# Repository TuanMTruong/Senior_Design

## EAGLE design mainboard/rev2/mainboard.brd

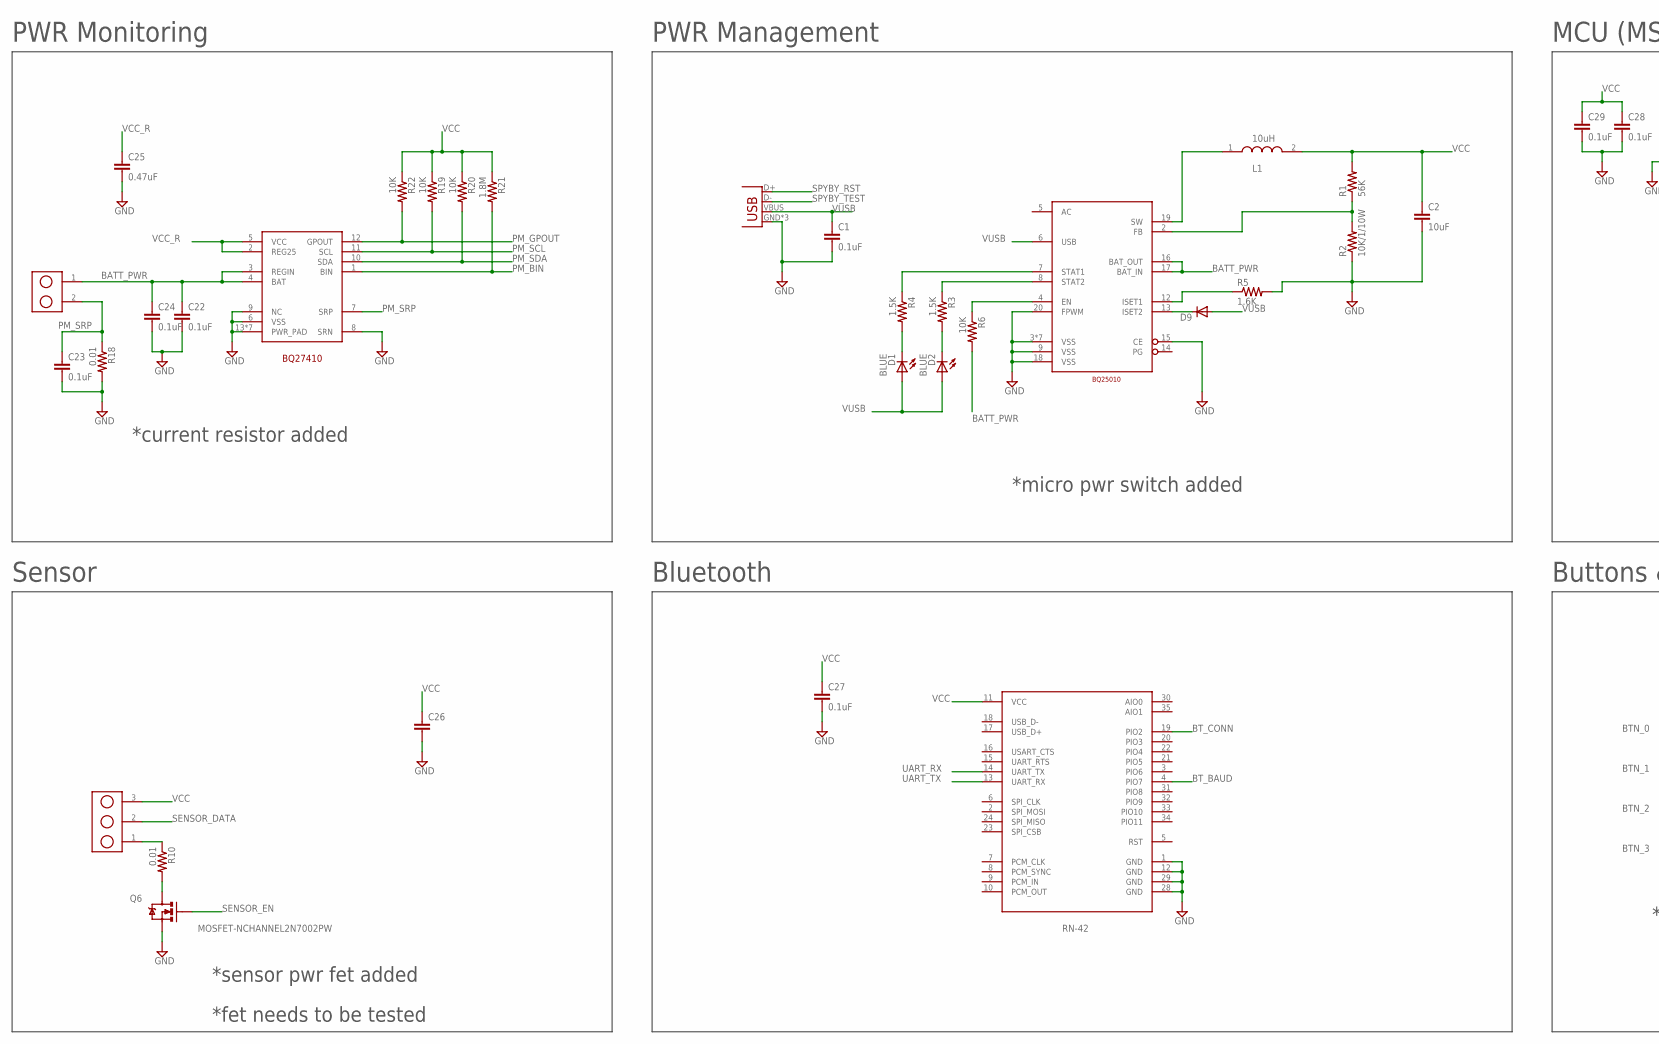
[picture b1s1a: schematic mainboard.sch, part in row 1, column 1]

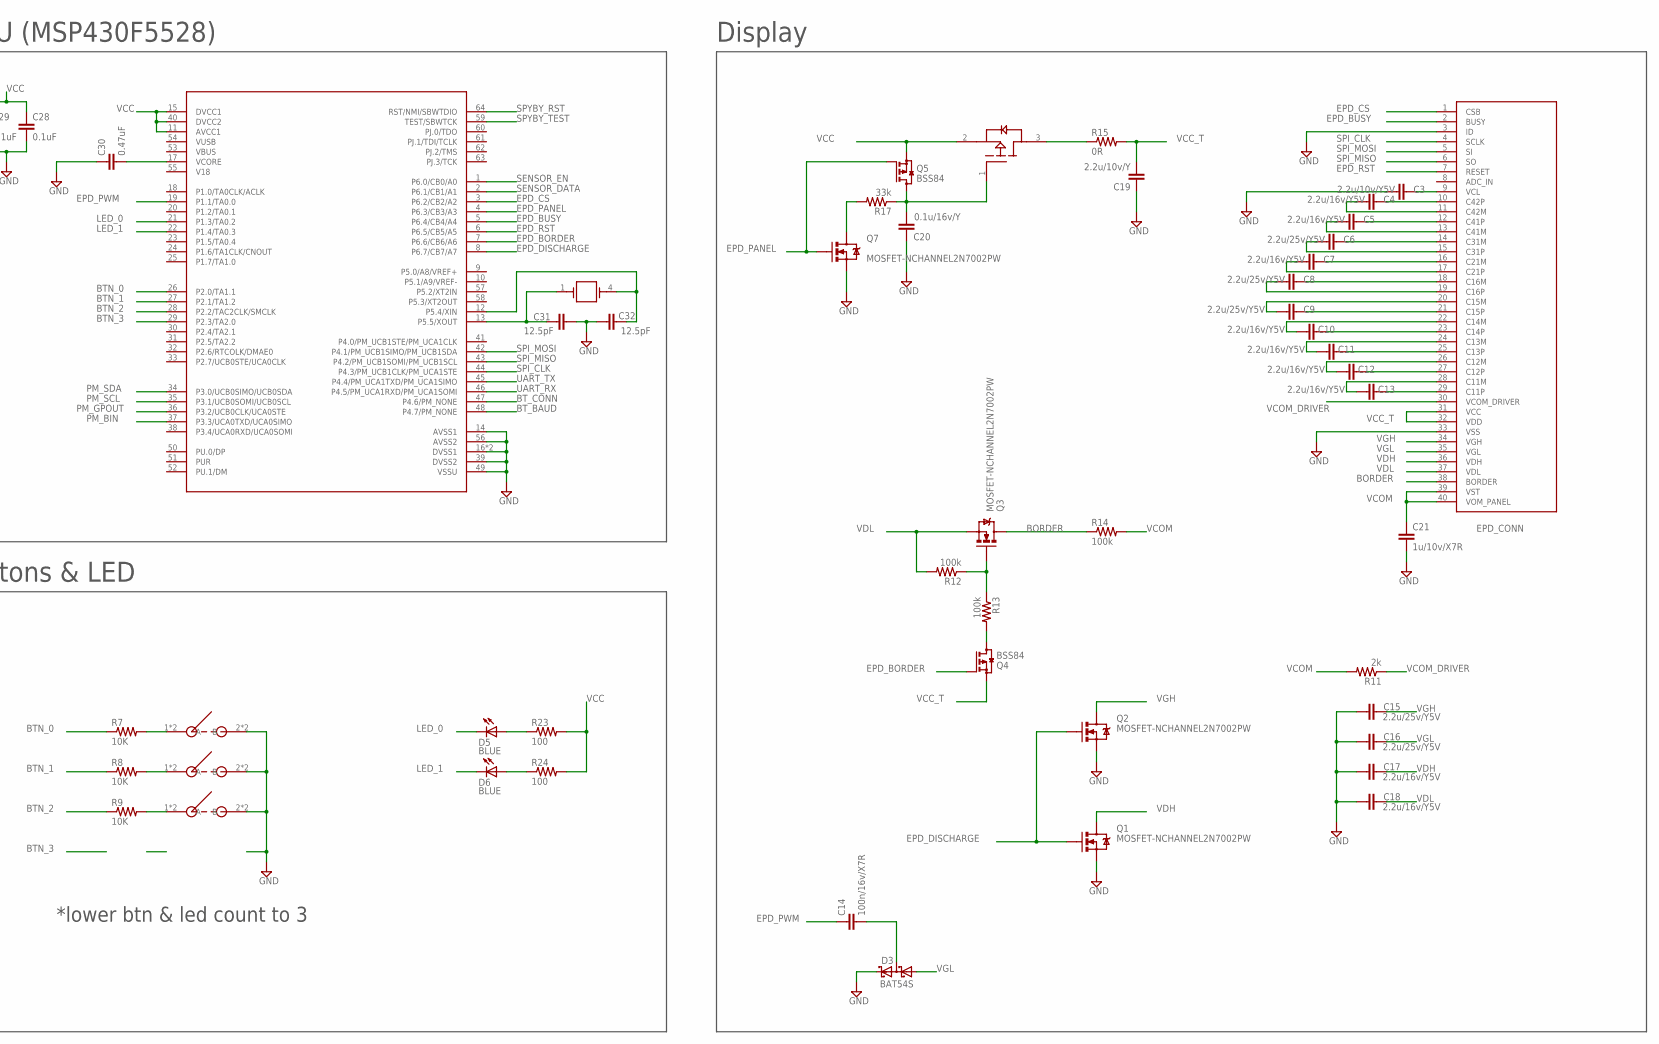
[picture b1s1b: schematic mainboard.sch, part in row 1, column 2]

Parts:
AP2305: DMG2305UX; SOT23
C1, C22, C23, C24, C27, C28, C29: 0.1uF; 0402-CAP
C2: 10uF; 0402-CAP
C3: 2.2u/10v/Y5V; 0402-CAP
C4, C5, C7, C10, C11, C12, C13, C17, C18: 2.2u/16v/Y5V; 0402-CAP
C6, C8, C9, C15, C16: 2.2u/25v/Y5V; 0402-CAP
C14: 100n/16v/X7R; 0402-CAP
C19: 2.2u/10v/Y; 0402-CAP
C20: 0.1u/16v/Y; 0402-CAP
C21: 1u/10v/X7R; 0402-CAP
C25, C30: 0.47uF; 0402-CAP
C26: CAP0402-CAP; 0402-CAP
C31, C32: 12.5pF; 0402-CAP
D1, D2, D5, D6: BLUE; LED-0603
D3: BAT54S; SOT23
D9: DIODESOD523; SOD523
JP1: USB-MICROB
L1: 10uH; ASPI_0428S-100M-T
Q1, Q2, Q3, Q6, Q7: MOSFET-NCHANNEL2N7002PW; SOT323
Q4, Q5: BSS84; SOT23
R1: 56K; 0402-RES
R2: 10K/1/10W; 0402-RES
R3, R4: 1.5K; 0402-RES
R5: 1.6K; 0402-RES
R6, R7, R8, R9, R19, R20, R22: 10K; 0402-RES
R10, R18: 0.01; 0402-RES
R11: 2k; 0402-RES
R12, R13, R14: 100k; 0402-RES
R15: 0R; 0402-RES
R17: 33k; 0402-RES
R21: 1.8M; 0402-RES
R23, R24: 100; 0402-RES
U$1: MSP430F5528; VQFN_RGC_64PIN
U$2: RN-42
U$3: BQ25010; VQFN_RHL_20PIN
U$4, U$5, U$6: RA_TAC_BUTTON"EVQPUK"; EVQ-PUK02K; PART# EVQ-PUK02K
U$8: FH12-40S-0.5SH
U$9: BQ27410; SON_DRZ_12PIN
U$11: HEADER_2PIN_50MIL
U$12: HEADER_3PIN_50MIL
X1: CRYSTAL"32.768"; ECS-327-12.5-17X-C-TR

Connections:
BATT_PWR: C22.1, C24.1, R6.2, U$3.16 (BAT_OUT), U$3.17 (BAT_IN), U$9.3 (REGIN), U$9.4 (BAT), U$11.1
BORDER: Q3.3 (D), R14.1, U$8.38 (BORDER)
BTN_0: R7.1, U$1.26 (P2.0/TA1.1)
BTN_1: R8.1, U$1.27 (P2.1/TA1.2)
BTN_2: R9.1, U$1.28 (P2.2/TAC2CLK/SMCLK)
BTN_3: U$1.29 (P2.3/TA2.0)
BT_BAUD: U$1.48 (P4.7/PM_NONE), U$2.4 (PIO7)
BT_CONN: U$1.47 (P4.6/PM_NONE), U$2.19 (PIO2)
EPD_BORDER: Q4.1 (G), U$1.7 (P6.6/CB6/A6)
EPD_BUSY: U$1.5 (P6.4/CB4/A4), U$8.2 (BUSY)
EPD_CS: U$1.3 (P6.2/CB2/A2), U$8.1 (CSB)
EPD_DISCHARGE: Q1.1 (G), Q2.1 (G), U$1.8 (P6.7/CB7/A7)
EPD_PANEL: Q5.1 (G), Q7.1 (G), U$1.4 (P6.3/CB3/A3)
EPD_PWM: C14.1, U$1.19 (P1.1/TA0.0)
EPD_RST: U$1.6 (P6.5/CB5/A5), U$8.7 (RESET)
GND: C1.2, C2.2, C3.1, C15.1, C16.1, C17.1, C18.1, C19.1, C20.1, C21.2, C22.2, C23.2, C24.2, C25.2, C26.2, C27.2, C28.2, C29.2, C30.1, C31.2, C32.1, D3.2 (C2), JP1.GND, JP1.MT1 (GND), JP1.MT2 (GND), Q1.2 (S), Q2.2 (S), Q6.2 (S), Q7.2 (S), R2.1, R5.2, R18.2, U$1.14 (AVSS1), U$1.16 (DVSS1), U$1.39 (DVSS2), U$1.49 (VSSU), U$1.56 (AVSS2), U$1.P$1 (DVSS1), U$2.1 (GND), U$2.12 (GND), U$2.28 (GND), U$2.29 (GND), U$3.3 (VSS), U$3.9 (VSS), U$3.15 (CE), U$3.18 (VSS), U$3.20 (FPWM), U$3.P$21 (VSS), U$3.P$22 (VSS), U$3.P$23 (VSS), U$3.P$24 (VSS), U$3.P$25 (VSS), U$3.P$26 (VSS), U$4.2 (B), U$4.4 (B), U$5.2 (B), U$5.4 (B), U$6.2 (B), U$6.4 (B), U$8.3 (ID), U$8.33 (VSS), U$9.6 (VSS), U$9.8 (SRN), U$9.9 (NC), U$9.13 (PWR_PAD), U$9.P$15 (PWR_PAD), U$9.P$16 (PWR_PAD), U$9.P$17 (PWR_PAD), U$9.P$18 (PWR_PAD), U$9.P$19 (PWR_PAD), U$9.P$20 (PWR_PAD)
LED_0: D5.C, U$1.21 (P1.3/TA0.2)
LED_1: D6.C, U$1.22 (P1.4/TA0.3)
unnamed: R5.1, U$3.12 (ISET1)
unnamed: D1.C, R4.2
unnamed: D9.C, U$3.13 (ISET2)
unnamed: D2.C, R3.2
unnamed: R1.1, R2.2, U$3.2 (FB)
unnamed: L1.1, U$3.19 (SW)
unnamed: C30.2, U$1.17 (VCORE)
unnamed: Q4.3 (D), R13.2
unnamed: C14.2, D3.3 (C1A2)
unnamed: R4.1, U$3.7 (STAT1)
unnamed: R3.1, U$3.8 (STAT2)
unnamed: R6.1, U$3.4 (EN)
unnamed: R7.2, U$4.1 (A), U$4.3 (A)
unnamed: R8.2, U$5.1 (A), U$5.3 (A)
unnamed: R9.2, U$6.1 (A), U$6.3 (A)
unnamed: Q6.3 (D), R10.2
unnamed: R10.1, U$12.1
unnamed: C4.2, U$8.10 (C42P)
unnamed: C4.1, U$8.11 (C42M)
unnamed: C5.2, U$8.12 (C41P)
unnamed: C5.1, U$8.13 (C41M)
unnamed: C6.2, U$8.14 (C31M)
unnamed: C6.1, U$8.15 (C31P)
unnamed: C7.2, U$8.16 (C21M)
unnamed: C7.1, U$8.17 (C21P)
unnamed: C8.2, U$8.18 (C16M)
unnamed: C8.1, U$8.19 (C16P)
unnamed: C9.1, U$8.20 (C15M)
unnamed: C9.2, U$8.21 (C15P)
unnamed: C10.1, U$8.22 (C14M)
unnamed: C10.2, U$8.23 (C14P)
unnamed: C11.1, U$8.24 (C13M)
unnamed: C11.2, U$8.25 (C13P)
unnamed: C12.1, U$8.26 (C12M)
unnamed: C12.2, U$8.27 (C12P)
unnamed: C13.1, U$8.28 (C11M)
unnamed: C13.2, U$8.29 (C11P)
unnamed: C3.2, U$8.9 (VCL)
unnamed: AP2305.3 (DRAIN), R15.1
unnamed: D5.A, R23.1
unnamed: Q3.1 (G), R12.1, R13.1
unnamed: AP2305.1 (GATE), C20.2, Q5.3 (D), R17.1
unnamed: D6.A, R24.1
unnamed: Q7.3 (D), R17.2
PM_BIN: R21.2, U$1.37 (P3.3/UCA0TXD/UCA0SIMO), U$9.1 (BIN)
PM_GPOUT: R22.2, U$1.36 (P3.2/UCB0CLK/UCA0STE), U$9.12 (GPOUT)
PM_SCL: R19.2, U$1.35 (P3.1/UCB0SOMI/UCB0SCL), U$9.11 (SCL)
PM_SDA: R20.2, U$1.34 (P3.0/UCB0SIMO/UCB0SDA), U$9.10 (SDA)
PM_SRP: C23.1, R18.1, U$9.7 (SRP), U$11.2
SENSOR_DATA: U$1.2 (P6.1/CB1/A1), U$12.2
SENSOR_EN: Q6.1 (G), U$1.1 (P6.0/CB0/A0)
SPI_CLK: U$1.44 (P4.3/PM_UCB1CLK/PM_UCA1STE), U$8.4 (SCLK)
SPI_MISO: U$1.43 (P4.2/PM_UCB1SOMI/PM_UCB1SCL), U$8.6 (SO)
SPI_MOSI: U$1.42 (P4.1/PM_UCB1SIMO/PM_UCB1SDA), U$8.5 (SI)
SPYBY_RST: JP1.D+, U$1.64 (RST/NMI/SBWTDIO)
SPYBY_TEST: JP1.D-, U$1.59 (TEST/SBWTCK)
UART_RX: U$1.46 (P4.5/PM_UCA1RXD/PM_UCA1SOMI), U$2.14 (UART_TX)
UART_TX: U$1.45 (P4.4/PM_UCA1TXD/PM_UCA1SIMO), U$2.13 (UART_RX)
VCC: AP2305.2 (SOURCE), C2.1, C26.1, C27.1, C28.1, C29.1, L1.2, Q5.2 (S), R1.2, R19.1, R20.1, R21.1, R22.1, R23.2, R24.2, U$1.11 (AVCC1), U$1.15 (DVCC1), U$1.40 (DVCC2), U$2.11 (VCC), U$12.3
VCC_R: C25.1, U$9.2 (REG25), U$9.5 (VCC)
VCC_T: C19.2, Q4.2 (S), R15.2, U$8.31 (VCC), U$8.32 (VDD)
VCOM: C21.1, R11.2, R14.2, U$8.39 (VST), U$8.40 (VOM_PANEL)
VCOM_DRIVER: R11.1, U$8.30 (VCOM_DRIVER)
VDH: C17.2, Q1.3 (D), U$8.36 (VDH)
VDL: C18.2, Q3.2 (S), R12.2, U$8.37 (VDL)
VGH: C15.2, Q2.3 (D), U$8.34 (VGH)
VGL: C16.2, D3.1 (A1), U$8.35 (VGL)
VUSB: C1.1, D1.A, D2.A, D9.A, JP1.VBUS, U$3.6 (USB)
XIN: C32.2, U$1.12 (P5.4/XIN), X1.4
XOUT: C31.1, U$1.13 (P5.5/XOUT), X1.1

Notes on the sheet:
MCU (MSP430F5528)
PWR Management
Bluetooth
Buttons & LED
Sensor
Display
PWR Monitoring
10uH
*micro pwr switch added
*sensor pwr fet added
*fet needs to be tested
*current resistor added
*lower btn & led count to 3

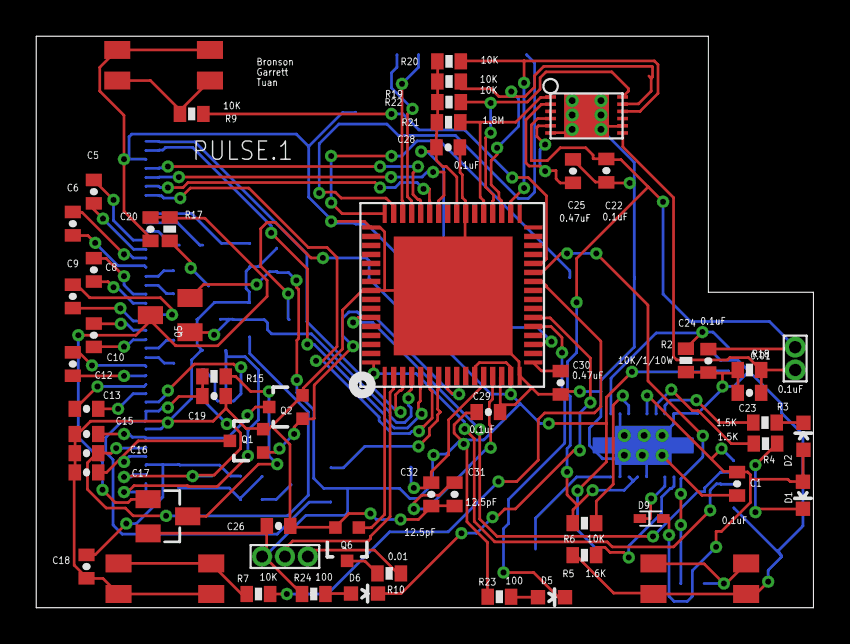
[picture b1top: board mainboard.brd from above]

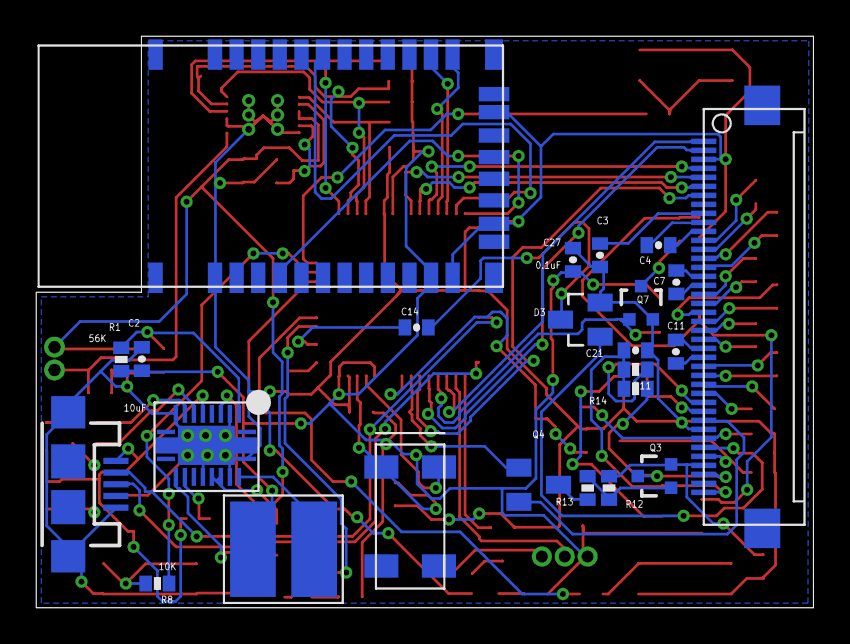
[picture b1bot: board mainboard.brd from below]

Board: 2 copper layers, 43.2 x 31.8 mm, 82 parts (24 on the bottom side), 87 nets.

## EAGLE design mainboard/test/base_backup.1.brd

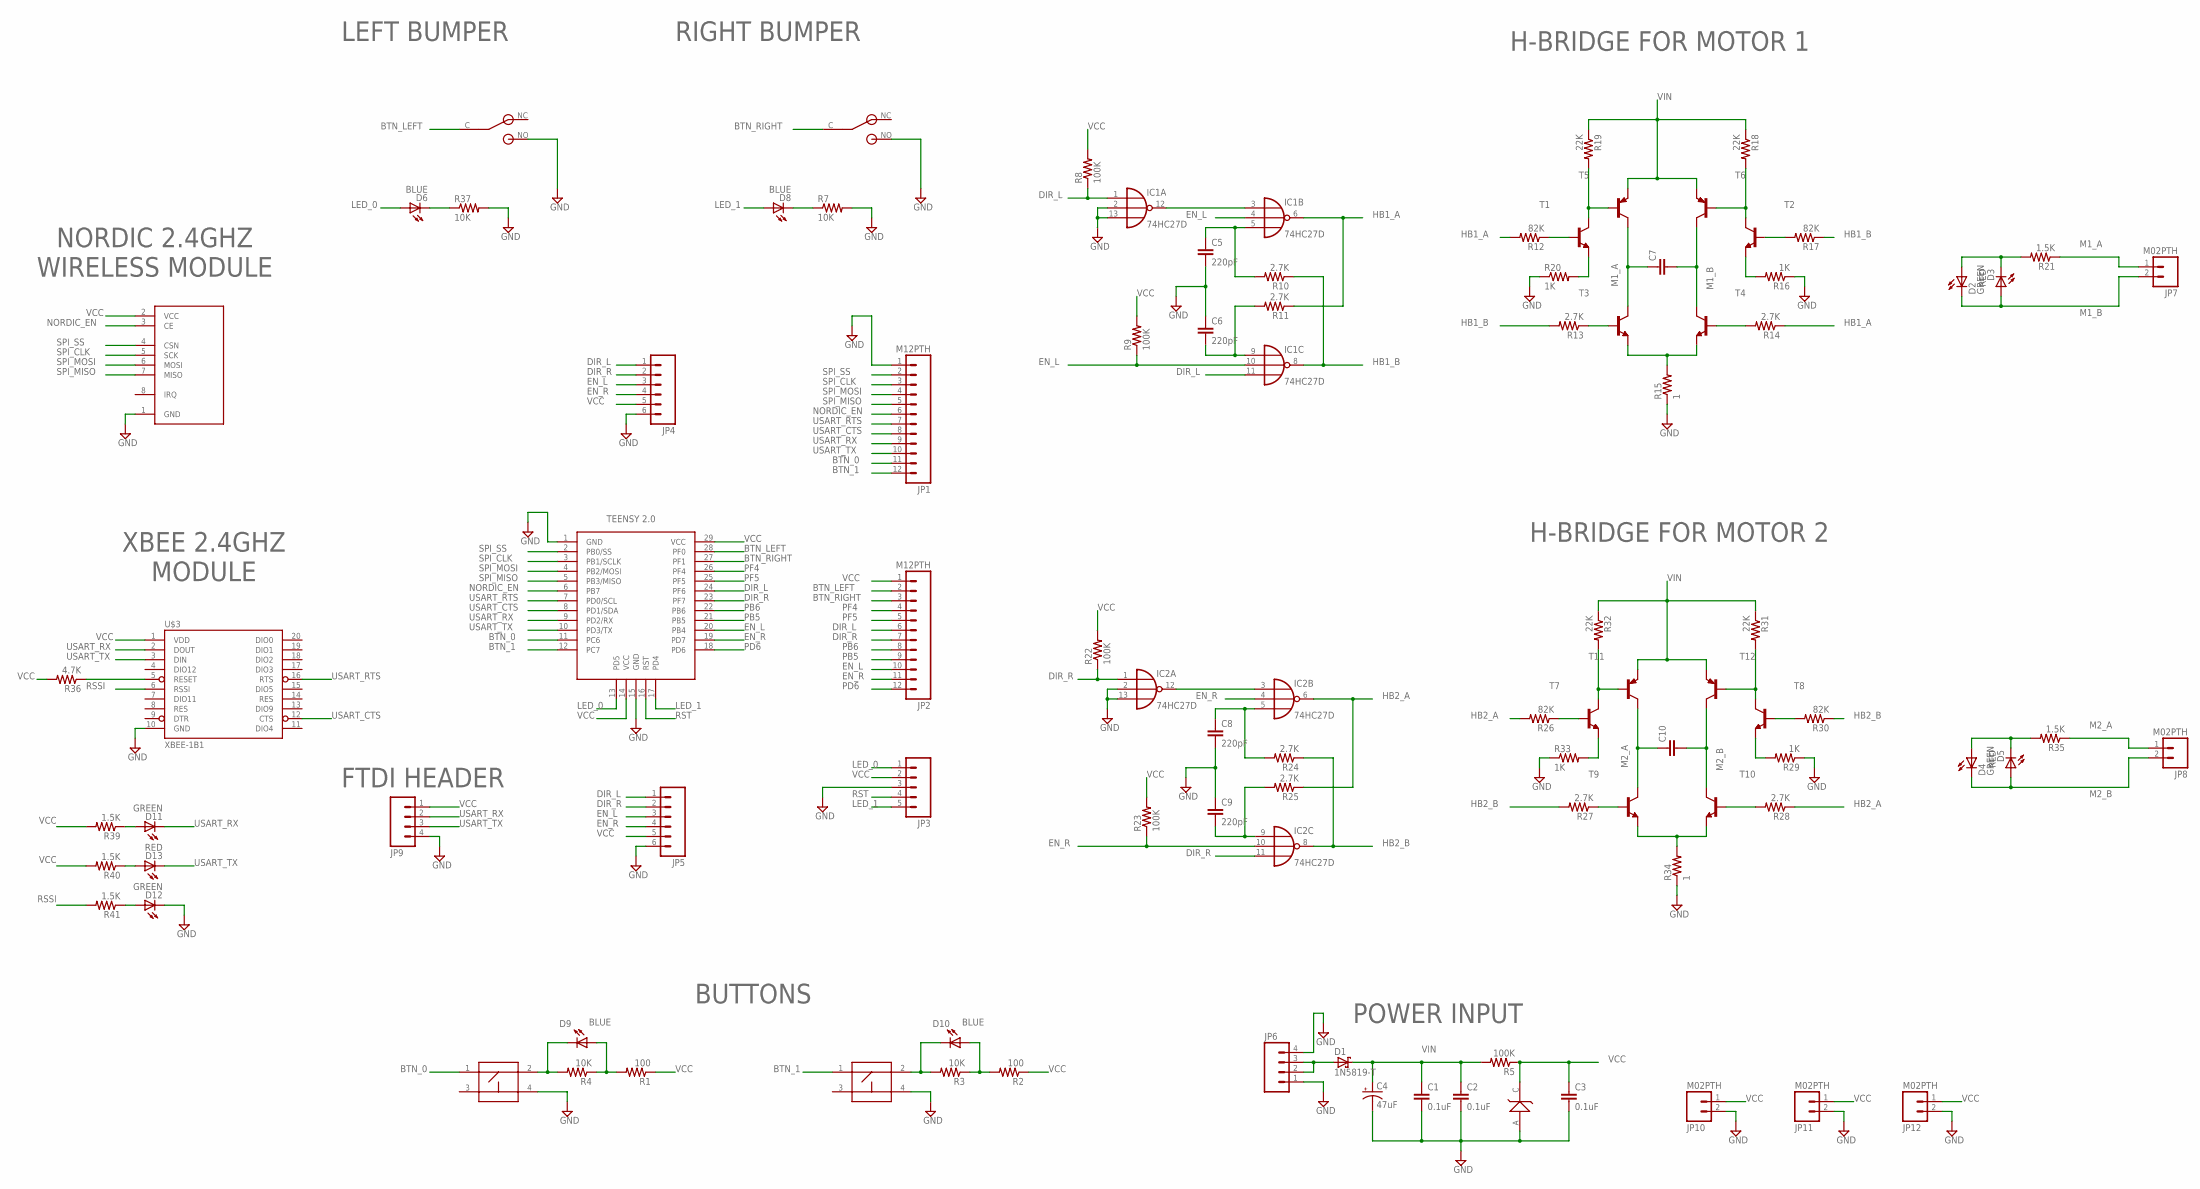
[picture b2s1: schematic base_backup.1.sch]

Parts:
C1, C2, C3: 0.1uF; 0603-CAP
C4: 47uF; PANASONIC_C
C5, C6, C8, C9: 220pF; 0603-CAP
C7, C10: CAP0603-CAP; 0603-CAP
D1: 1N5819-T; DO41-7.6
D2, D4, D11, D12: GREEN; LED-0603
D3, D5, D13: RED; LED-0603
D6, D8, D9, D10: BLUE; LED-0603
D7: 1N5819; DO41-7.6
IC1, IC2: 74HC27D; SO14
JP1, JP2: M12PTH; 1X12
JP3: M05PTH; 1X05
JP4, JP5: M06SIP; 1X06
JP6, JP9: M04PTH; 1X04
JP7, JP8, JP10, JP11, JP12: M02PTH; 1X02
R1, R2: 100; 0603-RES
R3, R4, R7, R37: 10K; 0603-RES
R5, R8, R9, R22, R23: 100K; 0603-RES
R10, R11, R13, R14, R24, R25, R27, R28: 2.7K; 0603-RES
R12, R17, R26, R30: 82K; 0603-RES
R15, R34: 1; 0603-RES
R16, R20, R29, R33: 1K; 0603-RES
R18, R19, R31, R32: 22K; 0603-RES
R21, R35, R39, R40, R41: 1.5K; 0603-RES
R36: 4.7K; 0603-RES
T1, T2, T3, T4, T7, T8, T9, T10: MMBT4401LT1-NPN-SOT23-BEC; SOT23-BEC
T5, T6, T11, T12: MMBT4403LT1-PNP-SOT23-BEC; SOT23-BEC
U$1: TEENSY2.0
U$2: NRF24L01
U$3: XBEE-1B1; XBEE-1
U$4, U$5: SPARKFUN_TAC_BUTTONS
U$6, U$7: SS075Q103F_BTN_RA; SS075Q103F020V1A

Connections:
BTN_0: JP1.11, U$1.11 (PC6), U$4.1
BTN_1: JP1.12, U$1.12 (PC7), U$5.1
BTN_LEFT: JP2.2, U$1.28 (PF0), U$6.C (COM)
BTN_RIGHT: JP2.3, U$1.27 (PF1), U$7.C (COM)
DIR_L: IC1.1 (I0), IC1.11 (I2), JP2.6, JP4.1, JP5.1, R8.1, U$1.24 (PF6)
DIR_R: IC2.1 (I0), IC2.11 (I2), JP2.7, JP4.2, JP5.2, R22.1, U$1.23 (PF7)
EN_L: IC1.4 (I1), IC1.10 (I1), JP2.10, JP4.3, JP5.3, R9.1, U$1.20 (PB4)
EN_R: IC2.4 (I1), IC2.10 (I1), JP2.11, JP4.4, JP5.4, R23.1, U$1.19 (PD7)
GND: C1.2, C2.2, C3.2, C4.-, C5.2, C6.1, C8.2, C9.1, D7.A, D12.C, IC1.2 (I1), IC1.7 (GND), IC1.13 (I2), IC2.2 (I1), IC2.7 (GND), IC2.13 (I2), JP1.1, JP3.3, JP4.6, JP5.6, JP6.1, JP6.4, JP9.4, JP10.2, JP11.2, JP12.2, R7.2, R15.1, R16.1, R20.1, R29.1, R33.1, R34.1, R37.2, U$1.1 (GND), U$1.15 (GND), U$2.1 (GND), U$3.10 (GND), U$4.4, U$5.4, U$6.NO, U$7.NO
HB1_A: IC1.6 (O), R11.1, R12.2, R14.1
HB1_B: IC1.8 (O), R10.1, R13.2, R17.1
HB2_A: IC2.6 (O), R25.1, R26.2, R28.1
HB2_B: IC2.8 (O), R24.1, R27.2, R30.1
LED_0: D6.A, JP3.1, U$1.13 (PD5)
LED_1: D8.A, JP3.5, U$1.17 (PD4)
M1_A: C7.1, JP7.1, R21.1, T3.C, T5.C
M1_B: C7.2, D2.C, D3.A, JP7.2, T4.C, T6.C
M2_A: C10.1, JP8.1, R35.1, T9.C, T11.C
M2_B: C10.2, D4.C, D5.A, JP8.2, T10.C, T12.C
unnamed: IC2.3 (I0), IC2.12 (O)
unnamed: C8.1, IC2.5 (I2), R24.2
unnamed: D9.A, R1.2, R4.1
unnamed: D9.C, R4.2, U$4.2
unnamed: C9.2, IC2.9 (I0), R25.2
unnamed: D10.A, R2.2, R3.1
unnamed: D10.C, R3.2, U$5.2
unnamed: R27.1, T9.B
unnamed: R32.2, T7.C, T11.B
unnamed: R31.2, T8.C, T12.B
unnamed: D1.A, JP6.2, JP6.3
unnamed: D6.C, R37.1
unnamed: D12.A, R41.1
unnamed: D13.A, R40.1
unnamed: D11.A, R39.1
unnamed: R30.2, T8.B
unnamed: C6.2, IC1.9 (I0), R11.2
unnamed: IC1.3 (I0), IC1.12 (O)
unnamed: R26.1, T7.B
unnamed: C5.1, IC1.5 (I2), R10.2
unnamed: R19.2, T1.C, T5.B
unnamed: R28.2, T10.B
unnamed: R20.2, T1.E
unnamed: R34.2, T9.E, T10.E
unnamed: R33.2, T7.E
unnamed: R29.2, T8.E
unnamed: D4.A, D5.C, R35.2
unnamed: R18.2, T2.C, T6.B
unnamed: R17.2, T2.B
unnamed: R13.1, T3.B
unnamed: R12.1, T1.B
unnamed: D8.C, R7.1
unnamed: R14.2, T4.B
unnamed: R15.2, T3.E, T4.E
unnamed: R16.2, T2.E
unnamed: D2.A, D3.C, R21.2
unnamed: R36.1, U$3.5 (RESET)
NORDIC_EN: JP1.6, U$1.6 (PB7), U$2.3 (CE)
PB5: JP2.9, U$1.21 (PB5)
PB6: JP2.8, U$1.22 (PB6)
PD6: JP2.12, U$1.18 (PD6)
PF4: JP2.4, U$1.26 (PF4)
PF5: JP2.5, U$1.25 (PF5)
RSSI: R41.2, U$3.6 (RSSI)
RST: JP3.4, U$1.16 (RST)
SPI_CLK: JP1.3, U$1.3 (PB1/SCLK), U$2.5 (SCK)
SPI_MISO: JP1.5, U$1.5 (PB3/MISO), U$2.7 (MISO)
SPI_MOSI: JP1.4, U$1.4 (PB2/MOSI), U$2.6 (MOSI)
SPI_SS: JP1.2, U$1.2 (PB0/SS), U$2.4 (CSN)
USART_CTS: JP1.8, U$1.8 (PD1/SDA), U$3.12 (CTS)
USART_RTS: JP1.7, U$1.7 (PD0/SCL), U$3.16 (RTS)
USART_RX: D11.C, JP1.9, JP9.2, U$1.9 (PD2/RX), U$3.2 (DOUT)
USART_TX: D13.C, JP1.10, JP9.3, U$1.10 (PD3/TX), U$3.3 (DIN)
VCC: C3.1, D7.C, IC1.14 (VCC), IC2.14 (VCC), JP2.1, JP3.2, JP4.5, JP5.5, JP9.1, JP10.1, JP11.1, JP12.1, R1.1, R2.1, R5.1, R8.2, R9.2, R22.2, R23.2, R36.2, R39.2, R40.2, U$1.14 (VCC), U$1.29 (VCC), U$2.2 (VCC), U$3.1 (VDD)
VIN: C1.1, C2.1, C4.+, D1.C, R5.2, R18.1, R19.1, R31.1, R32.1, T5.E, T6.E, T11.E, T12.E

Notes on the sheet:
LEFT BUMPER
RIGHT BUMPER
NORDIC 2.4GHZ WIRELESS MODULE
XBEE 2.4GHZ MODULE
FTDI HEADER
BUTTONS
POWER INPUT
H-BRIDGE FOR MOTOR 1
H-BRIDGE FOR MOTOR 2

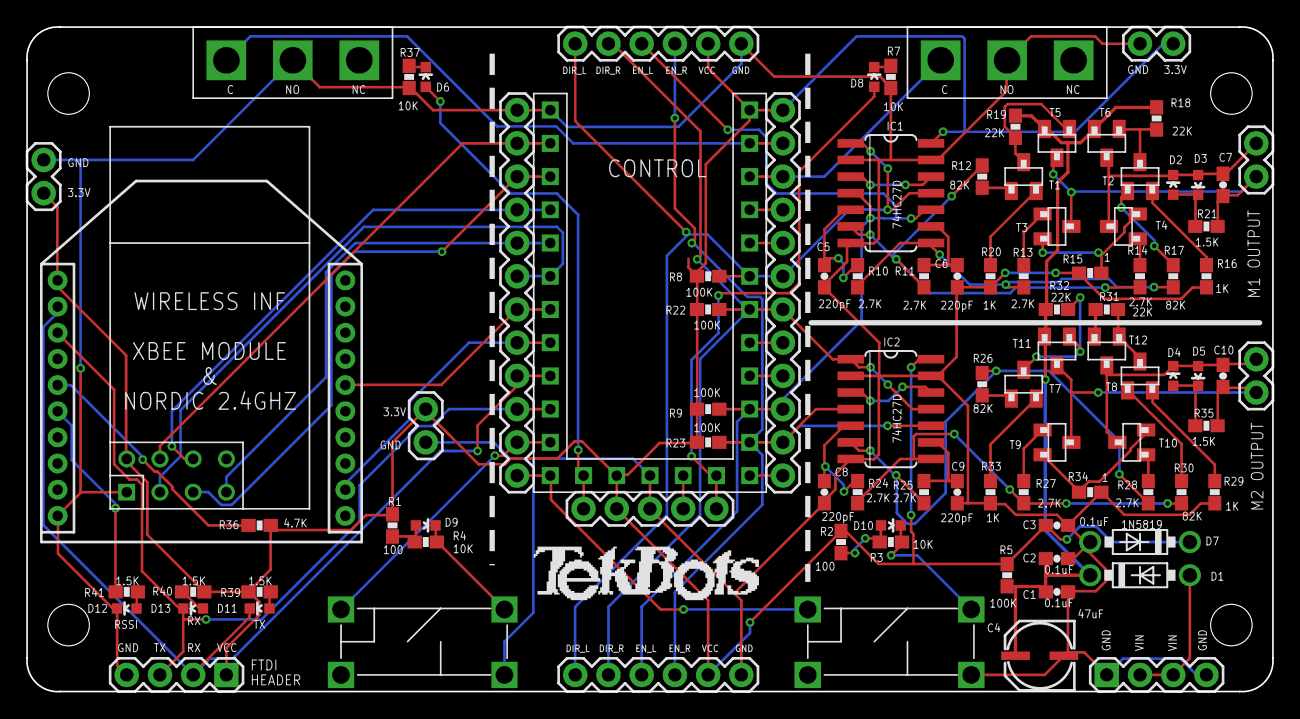
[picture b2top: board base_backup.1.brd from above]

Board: 2 copper layers, 95.3 x 50.8 mm, 95 parts (0 on the bottom side), 74 nets.

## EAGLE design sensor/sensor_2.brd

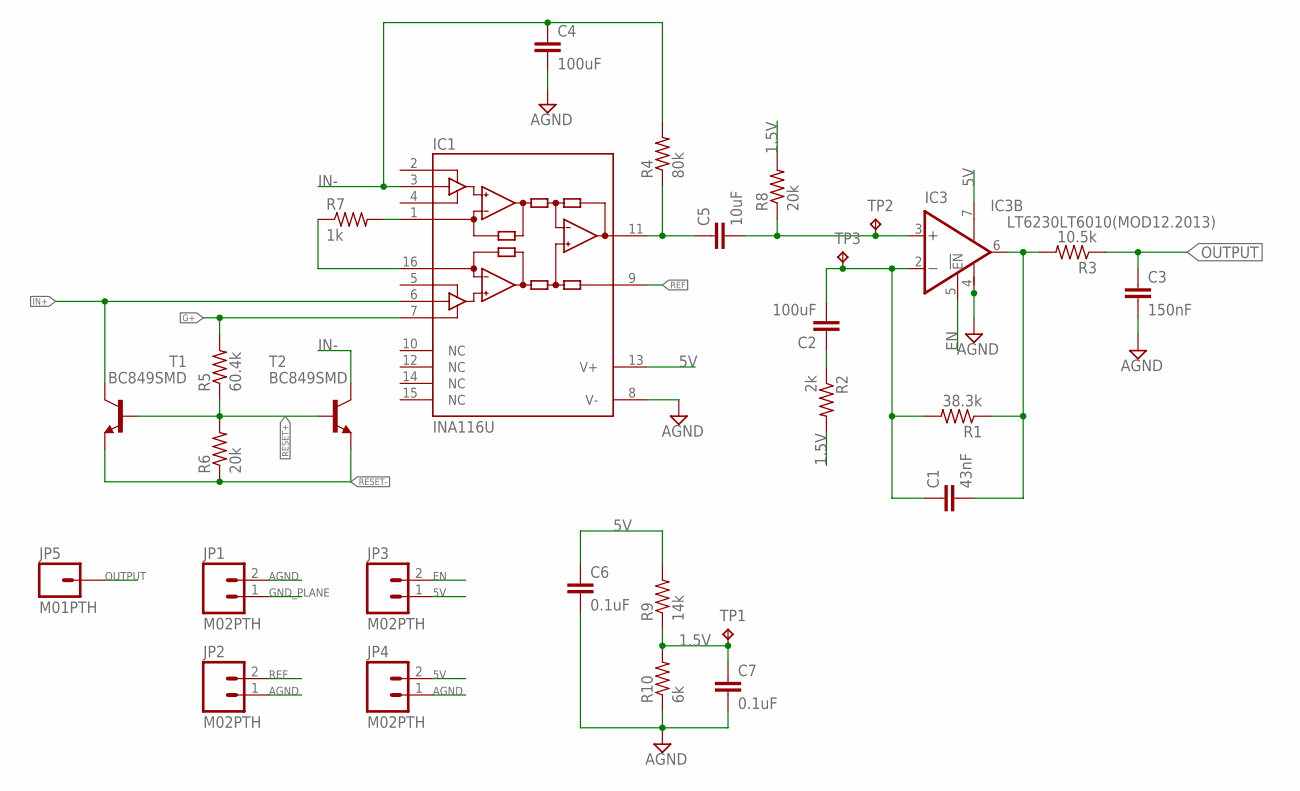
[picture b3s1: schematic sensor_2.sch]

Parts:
C1: 43nF; C0805
C2, C4: 100uF; C1206
C3: 150nF; C0603
C5: 10uF; C1206
C6, C7: 0.1uF; C0402
IC1: INA116U; SO16-1
IC3: LT6230LT6010(MOD12.2013); DFN8-3X3(MODIFIED12.2013)
JP1, JP2, JP3, JP4: M02PTH; 1X02
JP5: M01PTH; 1X01
R1: 38.3k; R0805
R2: 2k; R0805
R3: 10.5k; R0805
R4: 80k; R0805
R5: 60.4k; R0603
R6, R8: 20k; R0603
R7: 1k; R0402
R9: 14k; 0603-RES
R10: 6k; 1206
T1, T2: BC849SMD; SOT23-BEC
TP1, TP2, TP3: TPPAD1-13; P1-13

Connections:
1.5V: C7.1, R2.2, R8.2, R9.1, R10.2, TP1.TP
5V: C6.1, IC1.13 (V+), IC3.7 (V+), JP3.1, JP4.2, R9.2
AGND: C3.2, C4.2, C6.2, C7.2, IC1.8 (V-), IC3.4 (V-), JP1.2, JP2.1, JP4.1, R10.1
EN: IC3.5 (!EN), JP3.2
G+: IC1.7 (GUARD+), R5.2
GND_PLANE: JP1.1
IN+: IC1.6 (+IN), T1.C
IN-: C4.1, IC1.3 (-IN), R4.2, T2.C
unnamed: IC1.1 (RG), R7.2
unnamed: IC1.16 (RG), R7.1
unnamed: C5.1, IC1.11 (OUT), R4.1
unnamed: C2.1, R2.1
unnamed: C1.1, C2.2, IC3.2 (-IN), R1.2, TP3.TP
unnamed: C5.2, IC3.3 (+IN), R8.1, TP2.TP
unnamed: C1.2, IC3.6 (OUT), R1.1, R3.2
OUTPUT: C3.1, JP5.1, R3.1
REF: IC1.9 (REF), JP2.2
RESET+: R5.1, R6.2, T1.B, T2.B
RESET-: R6.1, T1.E, T2.E

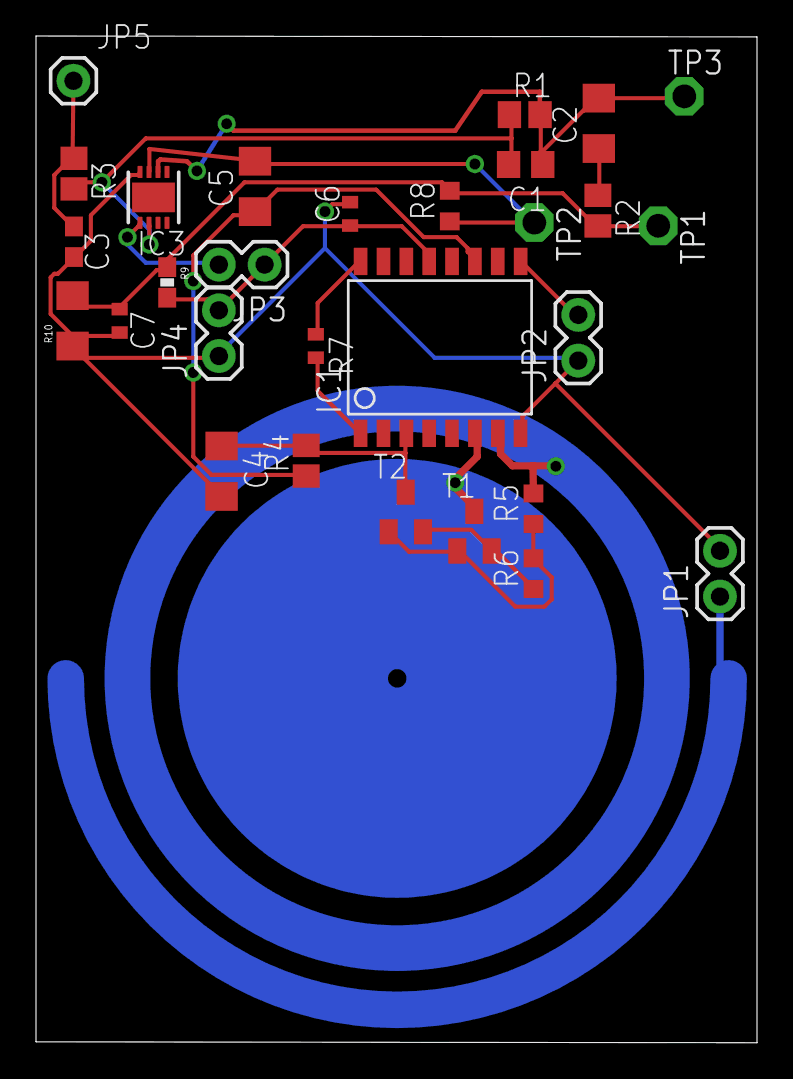
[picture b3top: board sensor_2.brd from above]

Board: 2 copper layers, 40.1 x 55.9 mm, 29 parts (0 on the bottom side), 18 nets.

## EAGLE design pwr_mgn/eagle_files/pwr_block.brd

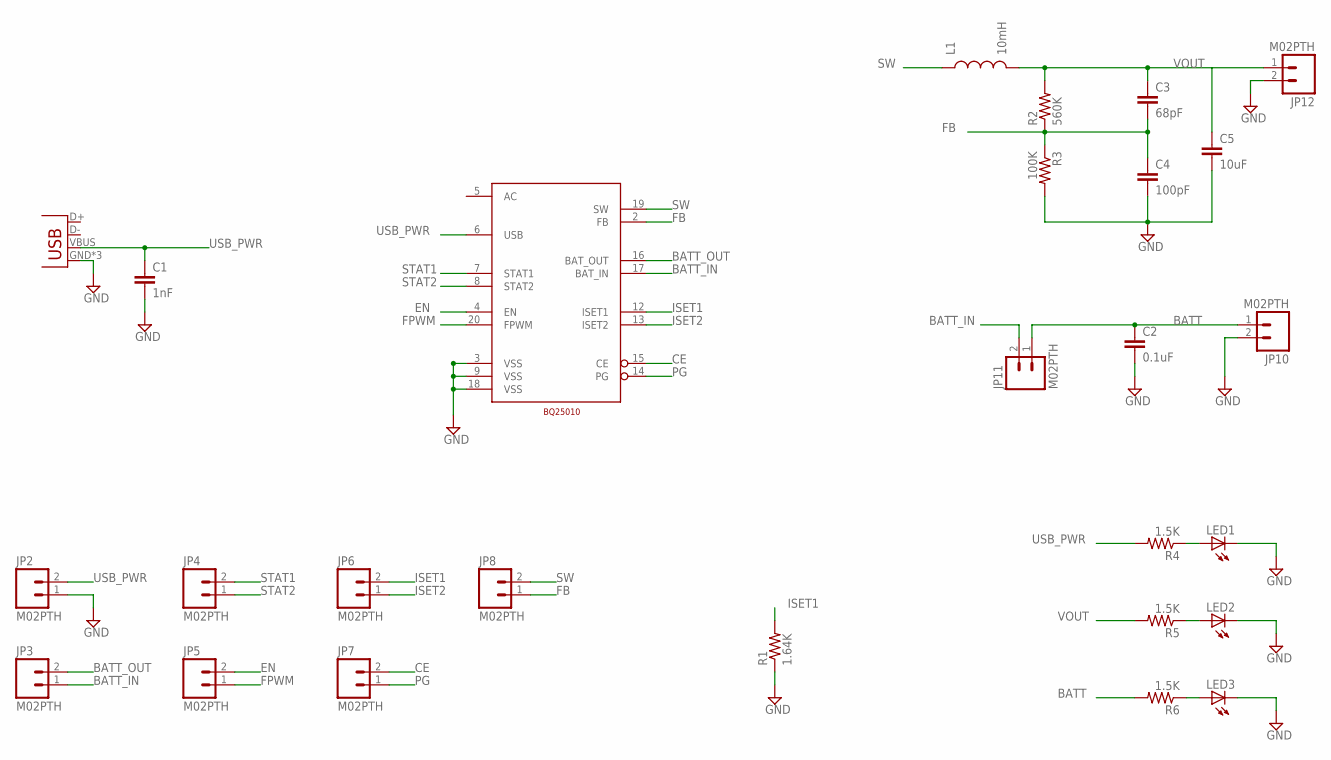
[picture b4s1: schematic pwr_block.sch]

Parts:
C1: 1nF; 0603-CAP
C2: 0.1uF; 0603-CAP
C3: 68pF; 0603-CAP
C4: 100pF; 0603-CAP
C5: 10uF; 0603-CAP
JP1: USB-MICROB
JP2, JP3, JP4, JP5, JP6, JP7, JP8, JP10, JP11, JP12: M02PTH; 1X02
L1: 10mH; 0603
LED1, LED2, LED3: LED0603; LED-0603
R1: 1.64K; 0603-RES
R2: 560K; 0603-RES
R3: 100K; 0603-RES
R4, R5, R6: 1.5K; 0603-RES
U$1: BQ25010; VQFN_RHL_20PIN

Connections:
BATT: C2.1, JP10.1, JP11.1, R6.2
BATT_IN: JP3.1, JP11.2, U$1.17 (BAT_IN)
BATT_OUT: JP3.2, U$1.16 (BAT_OUT)
CE: JP7.2, U$1.15 (CE)
EN: JP5.2, U$1.4 (EN)
FB: C3.2, C4.1, JP8.1, R2.1, R3.1, U$1.2 (FB)
FPWM: JP5.1, U$1.20 (FPWM)
GND: C1.2, C2.2, C4.2, C5.2, JP1.GND, JP1.MT1 (GND), JP1.MT2 (GND), JP2.1, JP10.2, JP12.2, LED1.C, LED2.C, LED3.C, R1.1, R3.2, U$1.3 (VSS), U$1.9 (VSS), U$1.18 (VSS)
ISET1: JP6.2, R1.2, U$1.12 (ISET1)
ISET2: JP6.1, U$1.13 (ISET2)
unnamed: LED1.A, R4.1
unnamed: LED2.A, R5.1
unnamed: LED3.A, R6.1
PG: JP7.1, U$1.14 (PG)
STAT1: JP4.2, U$1.7 (STAT1)
STAT2: JP4.1, U$1.8 (STAT2)
SW: JP8.2, L1.1, U$1.19 (SW)
USB_PWR: C1.1, JP1.VBUS, JP2.2, R4.2, U$1.6 (USB)
VOUT: C3.1, C5.1, JP12.1, L1.2, R2.2, R5.2

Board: 2 copper layers, 27 parts (0 on the bottom side), 19 nets, no tracks yet.

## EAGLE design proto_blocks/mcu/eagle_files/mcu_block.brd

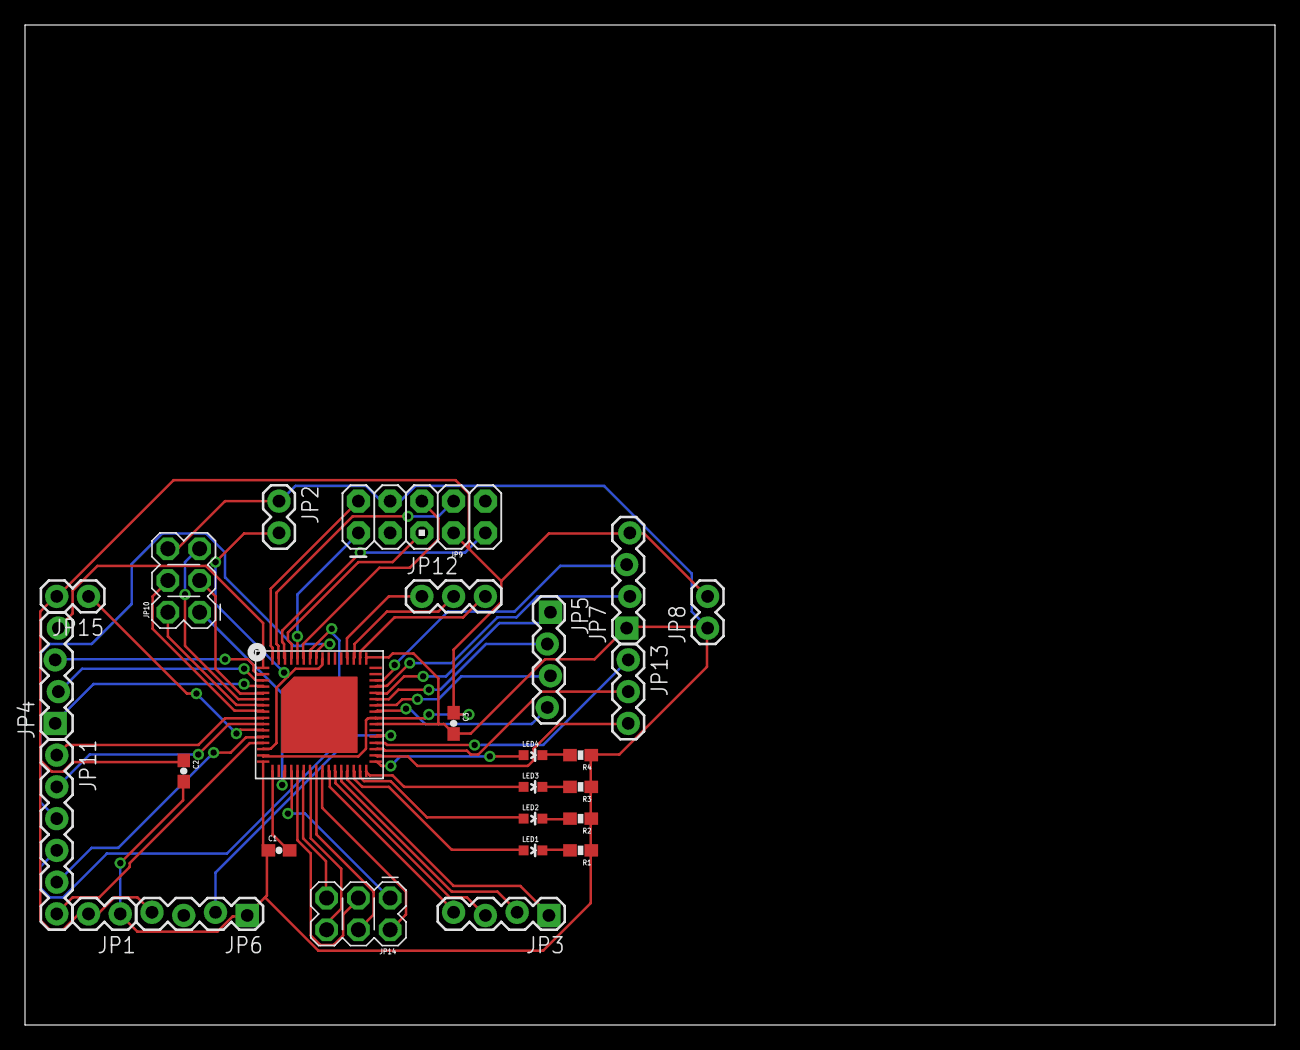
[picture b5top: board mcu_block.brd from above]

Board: 2 copper layers, 100.0 x 80.0 mm, 27 parts (0 on the bottom side), 58 nets.

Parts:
C1: 470nF; 0603-CAP
C2, C3: 0.1uF; 0603-CAP
JP1, JP2, JP8, JP15: M02PTH; 1X02
JP3, JP4, JP5, JP6, JP7: 1X04_LOCK
JP9: M05X2PTH; AVR_ICSP
JP10, JP14: 2X3_POGO
JP11: 1X06
JP12, JP13: 1X03
LED1, LED2, LED3, LED4: LED-0603
R1, R2, R3, R4: 1.5K; 0603-RES
U$1: MSP430F5528; VQFN_RGC_64PIN

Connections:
ADC_0: JP4.4, U$1.1
ADC_1: JP4.3, U$1.2
ADC_2: JP4.2, U$1.3
ADC_3: JP4.1, U$1.4
AGND: JP2.2, U$1.14, U$1.56
AVCC: JP15.1, U$1.11
BTN_0: JP3.4, U$1.26
BTN_1: JP3.3, U$1.27
BTN_2: JP3.2, U$1.28
BTN_3: JP3.1, U$1.29
DGND: C1.1, C2.2, C3.2, JP1.1, JP2.1, JP6.1, JP7.1, JP8.1, JP9.4, JP10.P$6, R1.1, R2.1, R3.1, R4.1, U$1.16, U$1.39, U$1.49
DISP_BORDER: JP10.P$2, U$1.7
DISP_BUSY: JP10.P$3, U$1.5
DISP_DISCHRG: JP10.P$4, U$1.8
DISP_PWM: JP10.P$1, U$1.19
DISP_RST: JP10.P$5, U$1.6
LED_0: LED1.A, U$1.30
LED_1: LED2.A, U$1.31
LED_2: LED3.A, U$1.32
LED_3: LED4.A, U$1.33
unnamed: C1.2, U$1.17
unnamed: LED4.C, R4.2
unnamed: JP11.1, U$1.9
unnamed: JP11.2, U$1.10
unnamed: JP11.3, U$1.57
unnamed: JP11.4, U$1.58
unnamed: JP11.5, U$1.12
unnamed: JP11.6, U$1.13
unnamed: JP12.3, U$1.50
unnamed: JP12.2, U$1.51
unnamed: JP12.1, U$1.52
unnamed: JP13.1, U$1.36
unnamed: JP13.2, U$1.35
unnamed: JP13.3, U$1.34
unnamed: LED3.C, R3.2
unnamed: LED2.C, R2.2
unnamed: LED1.C, R1.2
PWR_CE: JP14.P$1, U$1.20
PWR_FPWM: JP14.P$3, U$1.21
PWR_ISET2: JP14.P$4, U$1.24
PWR_PG: JP14.P$2, U$1.25
PWR_STAT1: JP14.P$5, U$1.22
PWR_STAT2: JP14.P$6, U$1.23
RST/NMI/SBWTDIO: JP9.2, U$1.64
SPI_CLK: JP5.1, U$1.44
SPI_MISO: JP5.2, U$1.43
SPI_MOSI: JP5.3, U$1.42
SPI_STE: JP5.4, U$1.41
TCK: JP9.8, U$1.63
TDI: JP9.5, U$1.61
TDO: JP9.1, U$1.60
TEST/SBWTCK: JP9.6, U$1.59
TMS: JP9.9, U$1.62
USART0_RX: JP6.3, U$1.38
USART0_TX: JP6.2, U$1.37
USART1_RX: JP7.3, U$1.46
USART1_TX: JP7.2, U$1.45
VCC: C2.1, C3.1, JP1.2, JP6.4, JP7.4, JP8.2, JP9.7, JP15.2, U$1.15, U$1.40

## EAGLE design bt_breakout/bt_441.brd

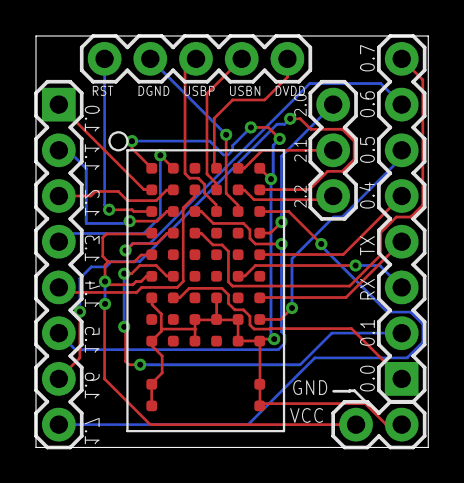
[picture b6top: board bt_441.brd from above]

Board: 2 copper layers, 21.8 x 22.9 mm, 6 parts (0 on the bottom side), 26 nets.

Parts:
JP1: M02PTH; 1X02
JP2: 1X03
JP4: 1X05
JP5, JP6: 1X08
U$1: PAN1720

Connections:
GND: JP1.1, U$1.A1, U$1.A7, U$1.A9, U$1.A11, U$1.A12, U$1.C8, U$1.C9, U$1.D7, U$1.D8, U$1.E8, U$1.E9, U$1.F1, U$1.F9, U$1.F11, U$1.F12
unnamed: JP1.2, U$1.A4, U$1.A5, U$1.A6
unnamed: JP4.5, U$1.D1
unnamed: JP4.4, U$1.D2
unnamed: JP4.3, U$1.D3
unnamed: JP4.2, U$1.E3
unnamed: JP4.1, U$1.A3
unnamed: JP5.1, U$1.B7
unnamed: JP5.2, U$1.B6
unnamed: JP5.3, U$1.E6
unnamed: JP5.4, U$1.F7
unnamed: JP5.5, U$1.F5
unnamed: JP5.6, U$1.F8
unnamed: JP5.7, U$1.B4
unnamed: JP5.8, U$1.C4
unnamed: JP6.1, U$1.A2
unnamed: JP6.2, U$1.B3
unnamed: JP6.3, U$1.B2
unnamed: JP6.4, U$1.B1
unnamed: JP6.5, U$1.C2
unnamed: JP6.6, U$1.C3
unnamed: JP6.7, U$1.F2
unnamed: JP6.8, U$1.F3
unnamed: JP2.1, U$1.F4
unnamed: JP2.2, U$1.E1
unnamed: JP2.3, U$1.E2

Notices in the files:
parts and their libraries:
SparkFun-Connectors: Licensing: CC v3.0 Share-Alike You are welcome to use this library for commercial purposes.
